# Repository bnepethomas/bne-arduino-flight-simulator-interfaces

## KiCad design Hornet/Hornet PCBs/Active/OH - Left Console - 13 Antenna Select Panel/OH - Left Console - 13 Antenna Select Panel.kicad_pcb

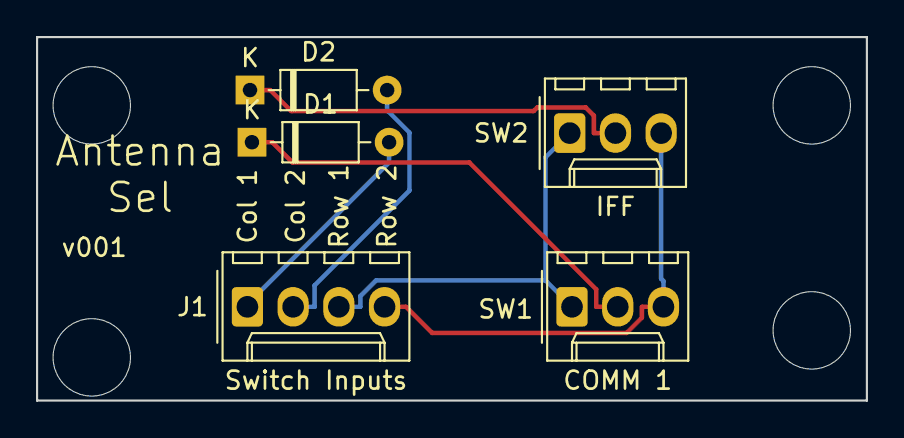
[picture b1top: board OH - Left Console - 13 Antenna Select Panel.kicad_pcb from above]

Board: 2 copper layers, 46.1 x 20.2 mm, 9 parts (0 on the bottom side), 6 nets.

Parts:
D1, D2: D; D_Signal_P7.62mm_Horizontal
H1, H2, H3, H4: MountingHole; MountingHole_4.3mm_M4
J1: Switch Inputs; Molex_1x04_P2.54mm_Vertical
SW1: COMM 1; Molex_1x03_P2.54mm_Vertical
SW2: IFF; Molex_1x03_P2.54mm_Vertical

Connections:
/Col1: D1.2, J1.1
/Col2: D2.2, J1.2
/Row1: J1.3, SW1.1, SW2.1
/Row2: J1.4, SW1.3, SW2.3
unnamed: D1.1, SW1.2
unnamed: D2.1, SW2.2

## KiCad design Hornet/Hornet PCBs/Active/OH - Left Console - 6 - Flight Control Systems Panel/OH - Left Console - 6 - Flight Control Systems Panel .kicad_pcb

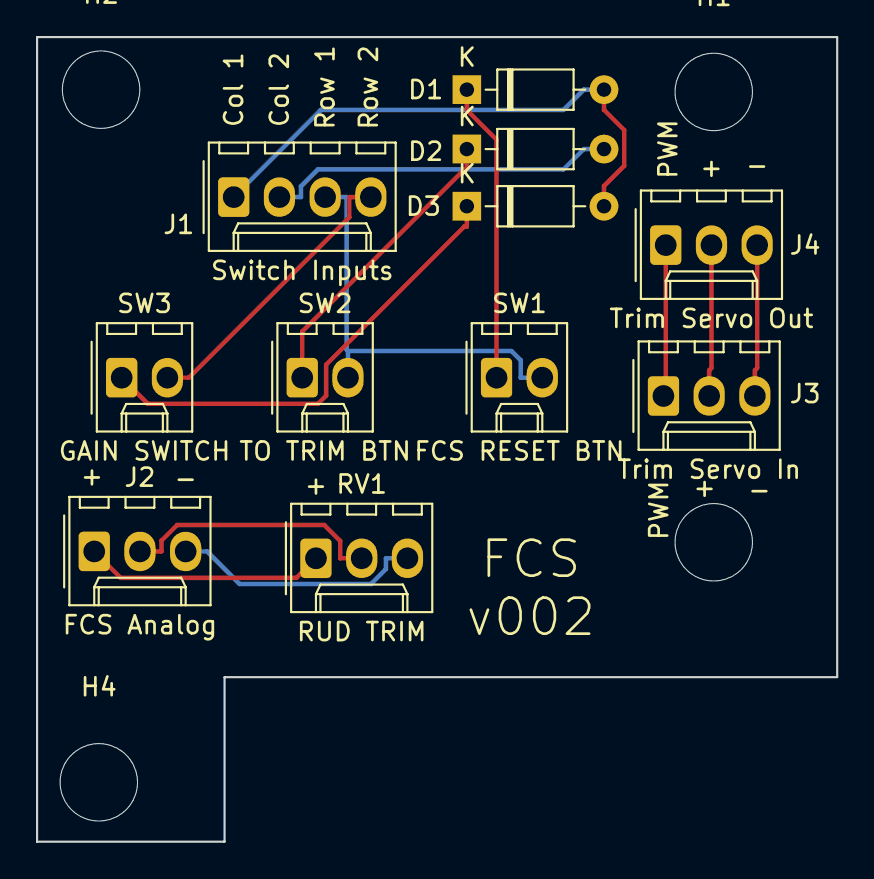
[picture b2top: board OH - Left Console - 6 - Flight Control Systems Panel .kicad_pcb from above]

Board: 2 copper layers, 44.5 x 44.7 mm, 15 parts (0 on the bottom side), 13 nets.

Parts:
D1, D2, D3: D; D_DO-35_SOD27_P7.62mm_Horizontal
H1, H2, H3, H4: MountingHole; MountingHole_4.3mm_M4
J1: Switch Inputs; Molex_1x04_P2.54mm_Vertical
J2: FCS Analog; Molex_1x03_P2.54mm_Vertical
J3: Trim Servo In; Molex_1x03_P2.54mm_Vertical
J4: Trim Servo Out; Molex_1x03_P2.54mm_Vertical
RV1: RUD TRIM; Molex_1x03_P2.54mm_Vertical
SW1: FCS RESET BTN; Molex_1x02_P2.54mm_Vertical
SW2: TO TRIM BTN; Molex_1x02_P2.54mm_Vertical
SW3: GAIN SWITCH; Molex_1x02_P2.54mm_Vertical

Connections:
/Analog+5V: J2.1, RV1.1
/Analog_Gnd: J2.3, RV1.3
/Col1: D1.2, D3.2, J1.1
/Col2: D2.2, J1.2
/Row1: J1.3, SW1.2, SW2.2
/Row2: J1.4, SW3.2
/Rud_Trim: J2.2, RV1.2
/SERVO_5V: J3.2, J4.2
/SERVO_GND: J3.3, J4.3
/TRIM_SERVO_SIG: J3.1, J4.1
unnamed: D1.1, SW1.1
unnamed: D2.1, SW2.1
unnamed: D3.1, SW3.1

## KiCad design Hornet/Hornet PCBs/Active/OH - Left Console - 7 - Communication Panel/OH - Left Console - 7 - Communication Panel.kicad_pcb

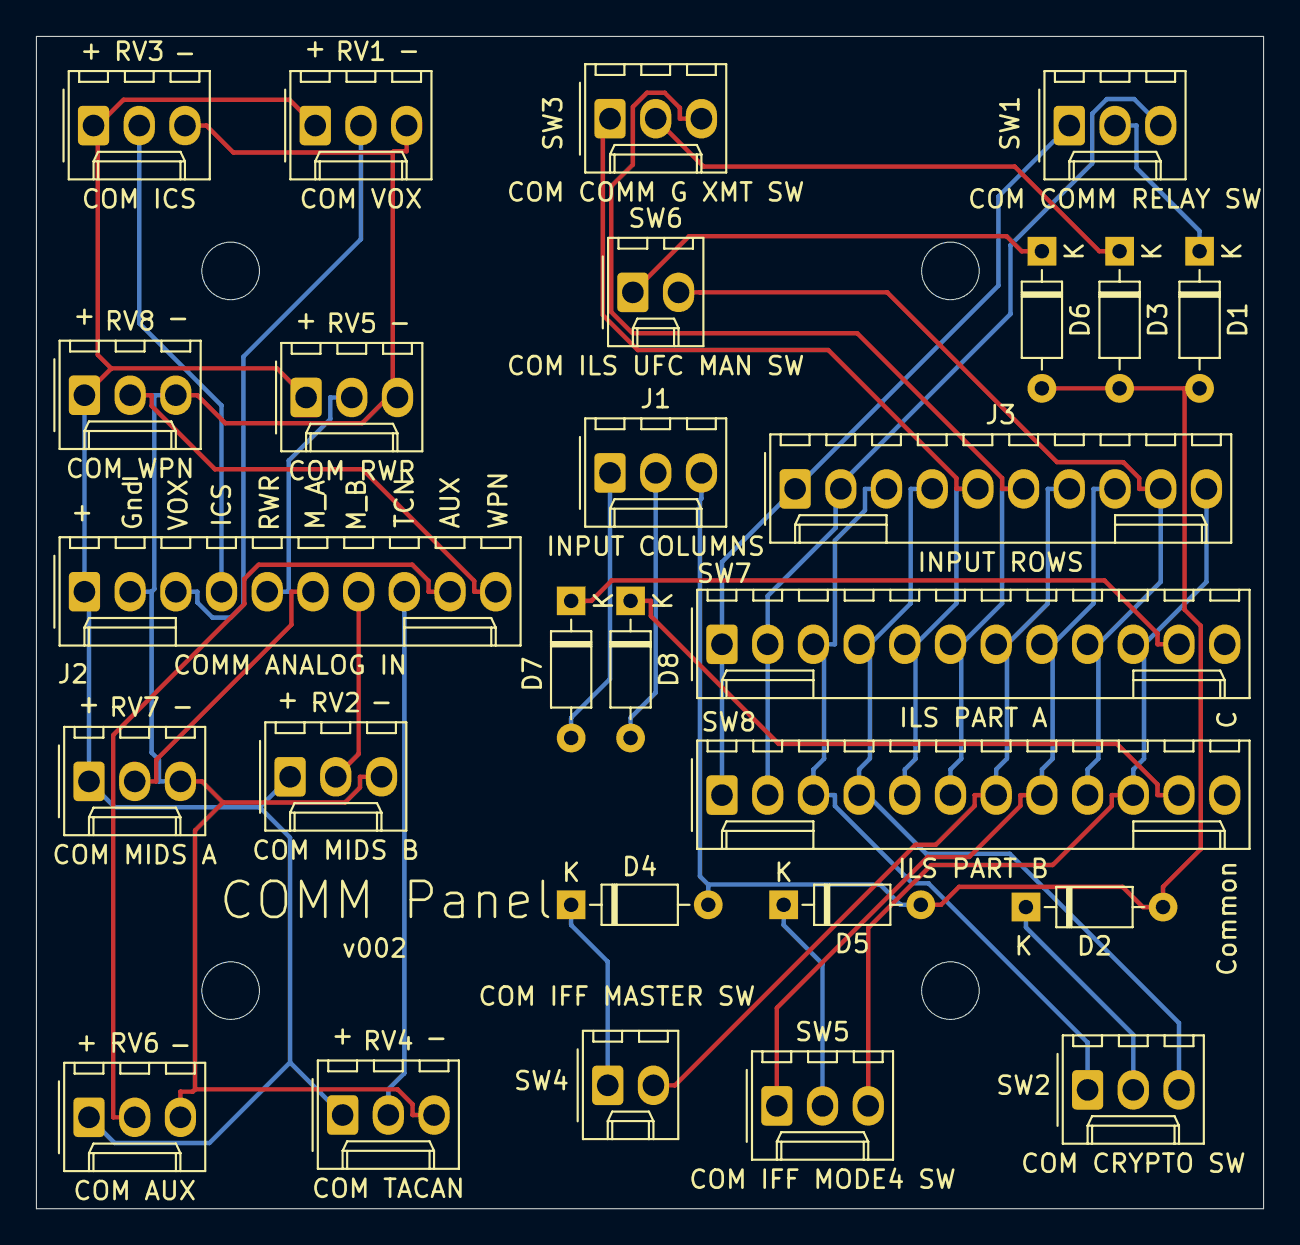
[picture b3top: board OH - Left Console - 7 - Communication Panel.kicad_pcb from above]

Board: 2 copper layers, 68.2 x 65.2 mm, 31 parts (0 on the bottom side), 31 nets.

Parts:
D1, D2, D3, D4, D5, D6, D7, D8: D; D_Signal_P7.62mm_Horizontal
H1, H2, H3, H4: MountingHole; MountingHole_3.2mm_M3
J1: INPUT COLUMNS; Molex_1x03_P2.54mm_Vertical
J2: COMM ANALOG IN; Molex_1x10_P2.54mm_Vertical
J3: INPUT ROWS; Molex_1x10_P2.54mm_Vertical
RV1: COM VOX; Molex_1x03_P2.54mm_Vertical
RV2: COM MIDS B; Molex_1x03_P2.54mm_Vertical
RV3: COM ICS; Molex_1x03_P2.54mm_Vertical
RV4: COM TACAN; Molex_1x03_P2.54mm_Vertical
RV5: COM RWR; Molex_1x03_P2.54mm_Vertical
RV6: COM AUX; Molex_1x03_P2.54mm_Vertical
RV7: COM MIDS A; Molex_1x03_P2.54mm_Vertical
RV8: COM_WPN; Molex_1x03_P2.54mm_Vertical
SW1: COM COMM RELAY SW; Molex_1x03_P2.54mm_Vertical
SW2: COM CRYPTO SW; Molex_1x03_P2.54mm_Vertical
SW3: COM COMM G XMT SW; Molex_1x03_P2.54mm_Vertical
SW4: COM IFF MASTER SW; Molex_1x02_P2.54mm_Vertical
SW5: COM IFF MODE4 SW; Molex_1x03_P2.54mm_Vertical
SW6: COM ILS UFC MAN SW; Molex_1x02_P2.54mm_Vertical
SW7: ILS PART A; Molex_KK-254_AE-6410-12A_1x12_P2.54mm_Vertical
SW8: ILS PART B; Molex_KK-254_AE-6410-12A_1x12_P2.54mm_Vertical

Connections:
/ANALOG_5V: J2.1, RV1.1, RV2.1, RV3.1, RV4.1, RV5.1, RV6.1, RV7.1, RV8.1
/ANALOG_GND: J2.2, RV1.3, RV2.3, RV3.3, RV4.3, RV5.3, RV6.3, RV7.3, RV8.3
/COL1: D7.2, J1.1
/COL2: D8.2, J1.2
/COL3: D1.2, D2.2, D3.2, D4.2, D5.2, D6.2, J1.3
/COM_AUX: J2.9, RV6.2
/COM_ICS: J2.4, RV3.2
/COM_MIDS_A: J2.6, RV7.2
/COM_MIDS_B: J2.7, RV2.2
/COM_RWR: J2.5, RV5.2
/COM_TACAN: J2.8, RV4.2
/COM_VOX: J2.3, RV1.2
/COM_WPN: J2.10, RV8.2
/ROW1: J3.1, SW1.1, SW7.1, SW8.1
/ROW2: J3.2, SW1.3, SW7.2, SW8.2
/ROW3: J3.3, SW2.1, SW7.3, SW8.3
/ROW4: J3.4, SW2.3, SW7.4, SW8.4
/ROW5: J3.5, SW3.1, SW7.5, SW8.5
/ROW6: J3.6, SW3.3, SW7.6, SW8.6
/ROW7: J3.7, SW4.2, SW7.7, SW8.7
/ROW8: J3.8, SW5.1, SW7.8, SW8.8
/ROW9: J3.9, SW6.2, SW7.9, SW8.9
/ROW10: J3.10, SW5.3, SW7.10, SW8.10
unnamed: D1.1, SW1.2
unnamed: D2.1, SW2.2
unnamed: D3.1, SW3.2
unnamed: D4.1, SW4.1
unnamed: D5.1, SW5.2
unnamed: D6.1, SW6.1
unnamed: D7.1, SW7.11
unnamed: D8.1, SW8.11

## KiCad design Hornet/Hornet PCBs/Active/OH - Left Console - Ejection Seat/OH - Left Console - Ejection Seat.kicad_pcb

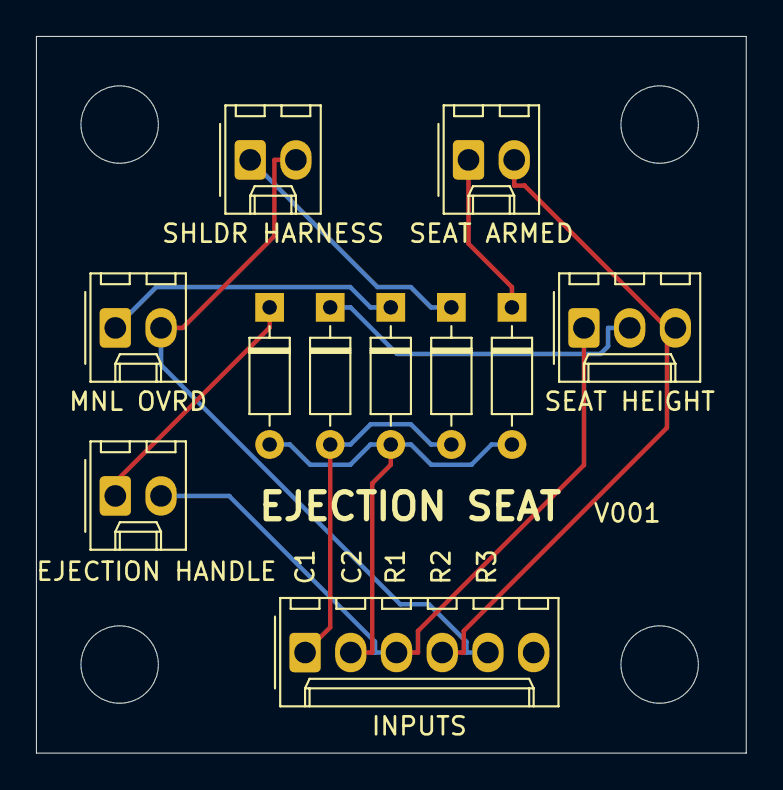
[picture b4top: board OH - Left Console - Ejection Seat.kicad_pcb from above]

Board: 2 copper layers, 39.4 x 39.8 mm, 15 parts (0 on the bottom side), 10 nets.

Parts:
D1, D2, D3, D4, D5: D; D_Signal_P7.62mm_Horizontal
H1, H2, H3, H4: MountingHole; MountingHole_4.3mm_M4
J1: INPUTS; Molex_1x06_P2.54mm_Vertical
SW1: EJECTION HANDLE; Molex_1x02_P2.54mm_Vertical
SW2: SEAT ARMED; Molex_1x02_P2.54mm_Vertical
SW3: MNL OVRD; Molex_1x02_P2.54mm_Vertical
SW4: SEAT HEIGHT; Molex_1x03_P2.54mm_Vertical
SW5: SHLDR HARNESS; Molex_1x02_P2.54mm_Vertical

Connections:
/Col1: D4.2, D5.2, J1.1
/Row1: J1.3, SW1.2, SW4.1
/Row2: J1.4, SW2.2, SW4.3
/Row3: J1.5, SW3.2, SW5.2
unnamed: D1.1, SW1.1
unnamed: D1.2, D2.2, D3.2, J1.2
unnamed: D2.1, SW2.1
unnamed: D3.1, SW3.1
unnamed: D4.1, SW4.2
unnamed: D5.1, SW5.1

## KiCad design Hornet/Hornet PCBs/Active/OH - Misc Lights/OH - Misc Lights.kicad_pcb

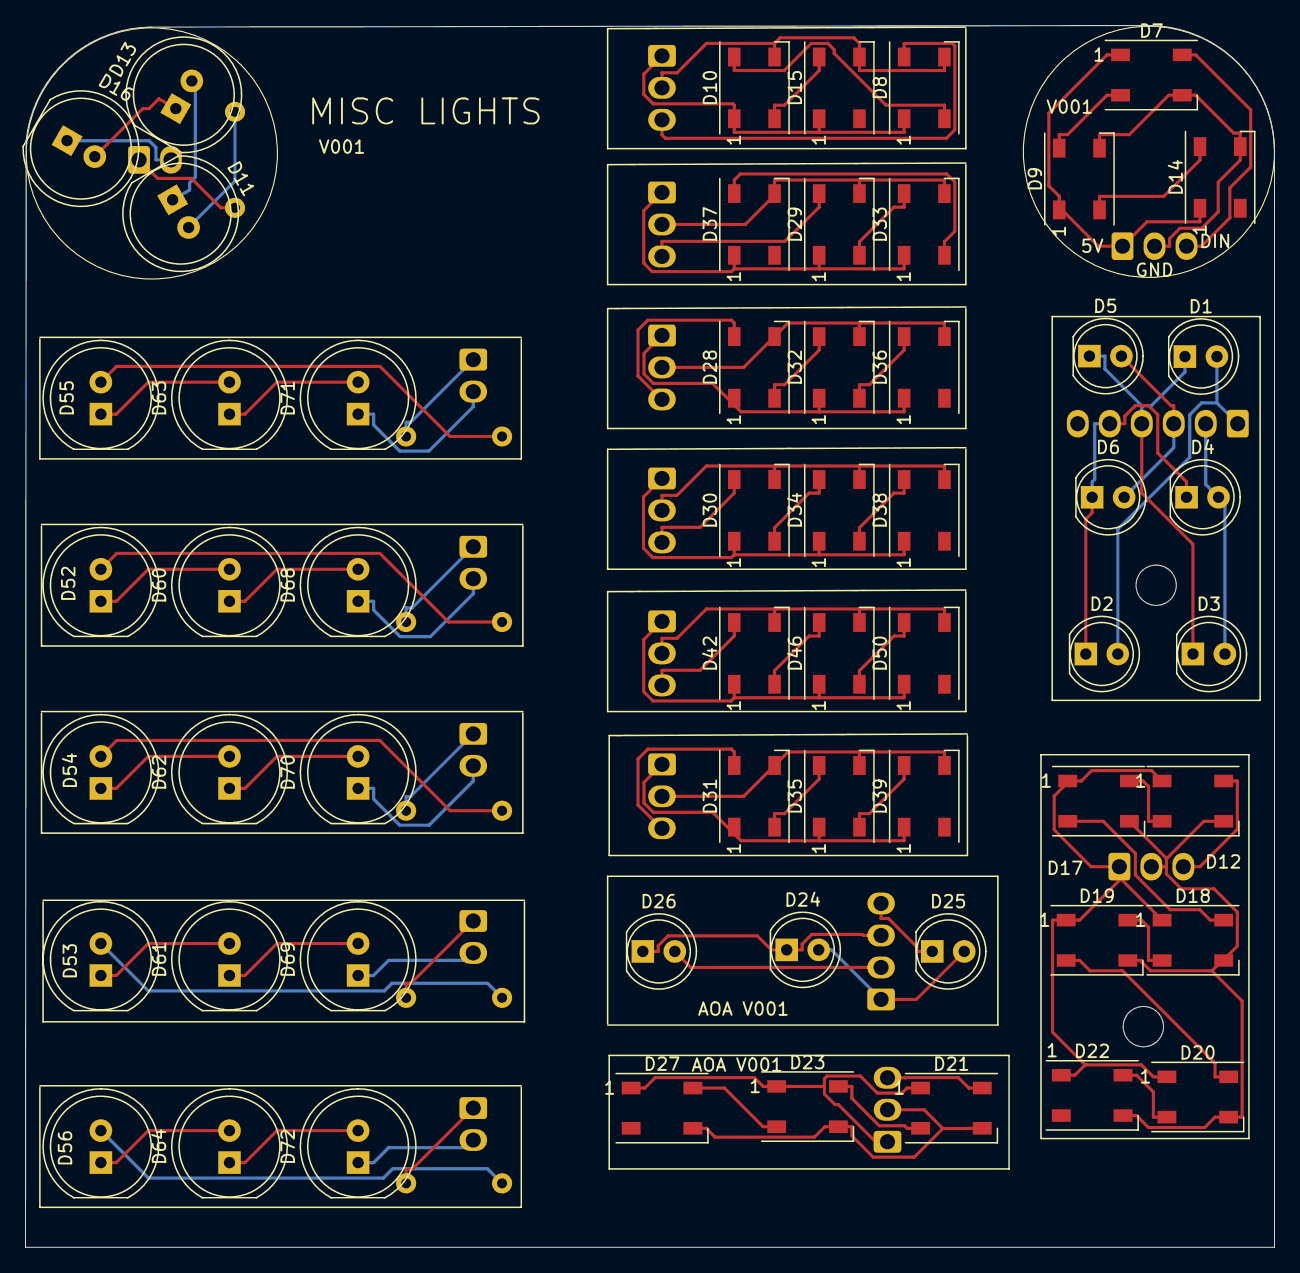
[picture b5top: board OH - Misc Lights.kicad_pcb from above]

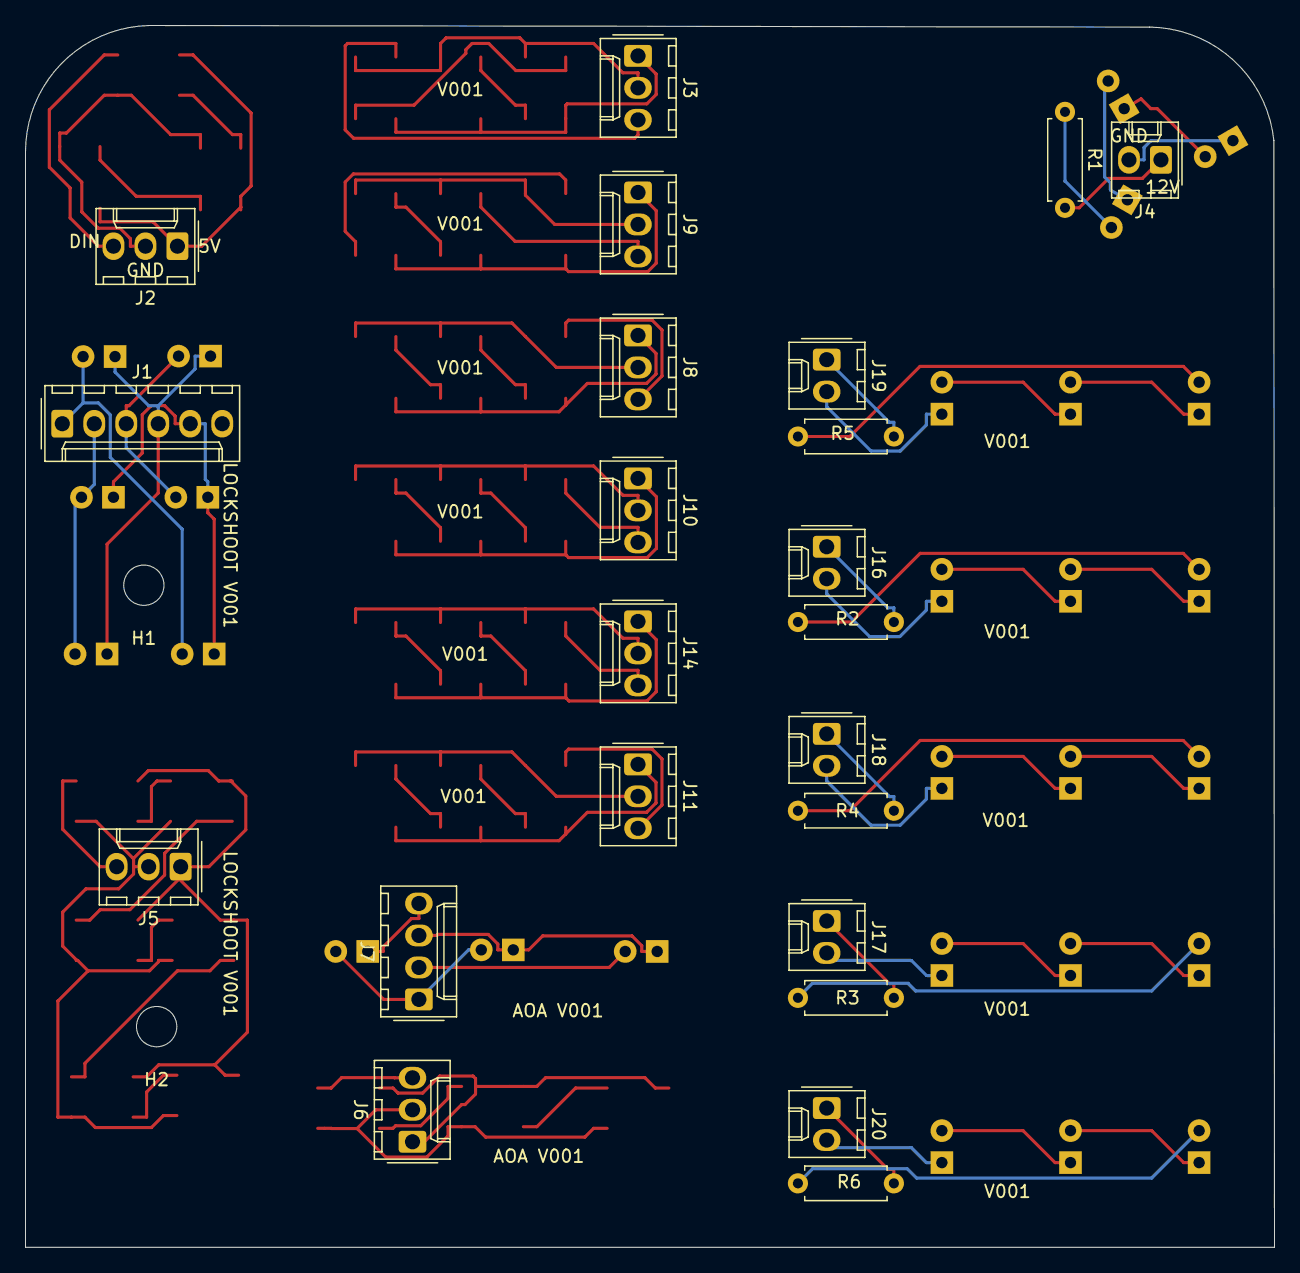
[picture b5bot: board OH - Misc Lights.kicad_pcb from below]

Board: 2 copper layers, 99.2 x 97.0 mm, 82 parts (25 on the bottom side), 87 nets.

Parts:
D1, D2, D3, D4, D5, D6, D24, D25, D26: LED; LED_D5.0mm
D7, D8, D9, D10, D12, D14, D15, D17, D18, D19, D20, D21, D22, D23, D27, D28, D29, D30, D31, D32, D33, D34, D35, D36, D37, D38, D39, D42, D46, D50: WS2812B; LED_WS2812B_PLCC4_5.0x5.0mm_P3.2mm
D11, D13, D16, D52, D53, D54, D55, D56, D60, D61, D62, D63, D64, D68, D69, D70, D71, D72: LED; LED_D8.0mm
H1, H2: MountingHole; MountingHole_3.2mm_M3
J1: Conn_01x06_Female; Molex_1x06_P2.54mm_Vertical
J2, J3, J5, J6, J8, J9, J10, J11, J14: Conn_01x03_Female; Molex_1x03_P2.54mm_Vertical
J4, J16, J17, J18, J19, J20: Conn_01x02_Female; Molex_1x02_P2.54mm_Vertical
J7: Conn_01x04_Female; Molex_1x04_P2.54mm_Vertical
R1, R2, R3, R4, R5, R6: R_US; R_Axial_DIN0207_L6.3mm_D2.5mm_P7.62mm_Horizontal

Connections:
/AOA_2812_+5V: D21.1, D23.1, D27.1, J6.1
/AOA_2812_GND: D21.3, D23.3, D27.3, J6.2
/AOA_2812_IN: D21.4, J6.3
/AOA_COL1: D24.2, D25.2, J7.1
/AOA_COL2: D26.2, J7.2
/AOA_ROW1: D24.1, D26.1, J7.3
/AOA_ROW2: D25.1, J7.4
/CHART_5V: J4.1, R1.2
/CHART_GND: D16.1, J4.2
/Col1: D1.2, D2.2, J1.1
/Col2: D3.2, D4.2, J1.2
/Col3: D5.2, D6.2, J1.3
/FLOOD_2812_+5V: D7.1, D9.1, D14.1, J2.1
/FLOOD_2812_GND: D7.3, D9.3, D14.3, J2.2
/FLOOD_2812_IN: D7.4, J2.3
/LOCKSHOOT_2812_+5V: D12.1, D17.1, D18.1, D19.1, D20.1, D22.1, J5.1
/LOCKSHOOT_2812_GND: D12.3, D17.3, D18.3, D19.3, D20.3, D22.3, J5.2
/LOCKSHOOT_IN: D12.4, J5.3
/Row1: D1.1, D3.1, D5.1, J1.4
/Row2: D2.1, D4.1, D6.1, J1.5
unnamed: D7.2, D9.4
unnamed: D8.4, J3.3
unnamed: D8.1, D10.1, D15.1, J3.1
unnamed: D10.2, D15.4
unnamed: D8.3, D10.3, D15.3, J3.2
unnamed: D8.2, D10.4
unnamed: D11.1, D13.2
unnamed: D11.2, R1.1
unnamed: D12.2, D17.4
unnamed: D13.1, D16.2
unnamed: D9.2, D14.4
unnamed: D17.2, D18.4
unnamed: D18.2, D19.4
unnamed: D19.2, D20.4
unnamed: D20.2, D22.4
unnamed: D21.2, D23.4
unnamed: D23.2, D27.4
unnamed: D28.1, D32.1, D36.1, J8.1
unnamed: D28.2, D32.4
unnamed: D28.3, D32.3, D36.3, J8.2
unnamed: D28.4, J8.3
unnamed: D29.1, D33.1, D37.1, J9.1
unnamed: D29.2, D33.4
unnamed: D29.3, D33.3, D37.3, J9.2
unnamed: D29.4, J9.3
unnamed: D30.1, D34.1, D38.1, J10.1
unnamed: D30.2, D34.4
unnamed: D30.3, D34.3, D38.3, J10.2
unnamed: D30.4, J10.3
unnamed: D31.1, D35.1, D39.1, J11.1
unnamed: D31.2, D35.4
unnamed: D31.3, D35.3, D39.3, J11.2
unnamed: D31.4, J11.3
unnamed: D32.2, D36.4
unnamed: D33.2, D37.4
unnamed: D34.2, D38.4
unnamed: D35.2, D39.4
unnamed: D42.1, D46.1, D50.1, J14.1
unnamed: D42.2, D46.4
unnamed: D42.3, D46.3, D50.3, J14.2
unnamed: D42.4, J14.3
unnamed: D46.2, D50.4
unnamed: D52.1, D60.2
unnamed: D52.2, R2.1
unnamed: D53.1, D61.2
unnamed: D53.2, R3.1
unnamed: D54.1, D62.2
unnamed: D54.2, R4.1
unnamed: D55.1, D63.2
unnamed: D55.2, R5.1
unnamed: D56.1, D64.2
unnamed: D56.2, R6.1
unnamed: D60.1, D68.2
unnamed: D61.1, D69.2
unnamed: D62.1, D70.2
unnamed: D63.1, D71.2
unnamed: D64.1, D72.2
unnamed: D68.1, J16.2
unnamed: D69.1, J17.2
unnamed: D70.1, J18.2
unnamed: D71.1, J19.2
unnamed: D72.1, J20.2
unnamed: J16.1, R2.2
unnamed: J17.1, R3.2
unnamed: J18.1, R4.2
unnamed: J19.1, R5.2
unnamed: J20.1, R6.2

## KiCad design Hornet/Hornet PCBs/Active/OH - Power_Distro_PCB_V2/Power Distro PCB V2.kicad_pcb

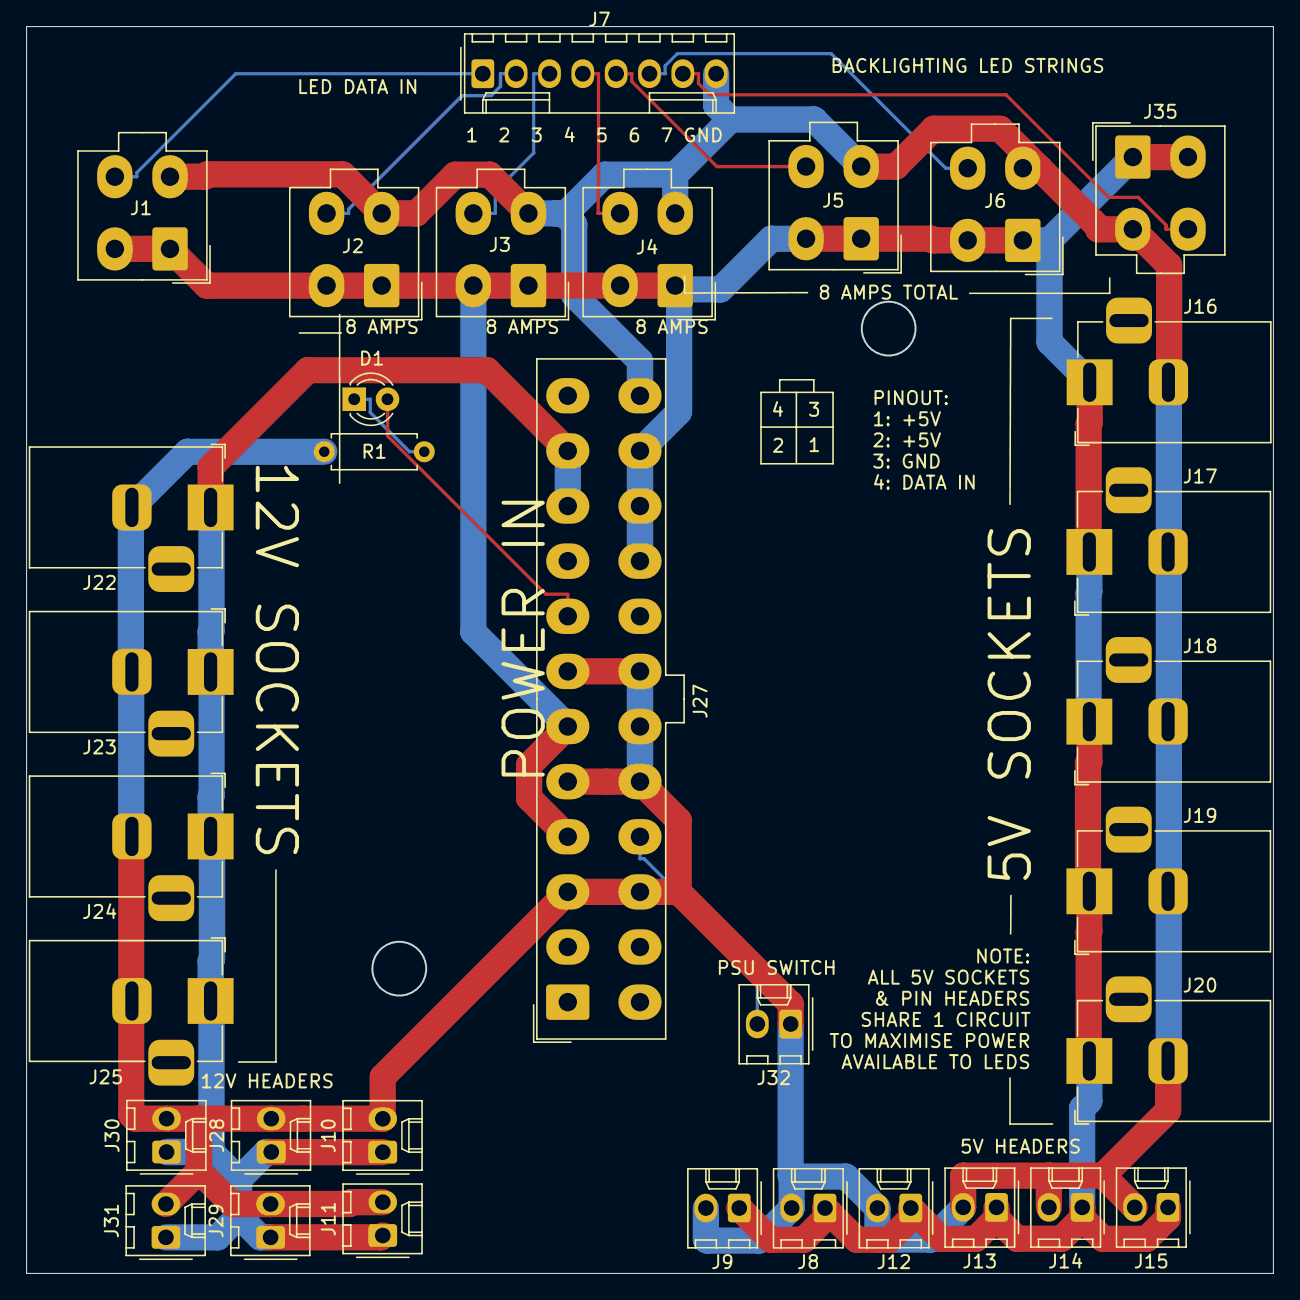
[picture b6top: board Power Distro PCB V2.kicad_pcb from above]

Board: 2 copper layers, 95.0 x 95.0 mm, 33 parts (0 on the bottom side), 13 nets.

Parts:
D1: LED; LED_D3.0mm
J1, J2, J3, J4, J5, J6, J35: Conn_01x04_Female; Molex_Mini-Fit_Jr_5566-04A_2x02_P4.20mm_Vertical
J7: Conn_01x08_Female; Molex_1x08_P2.54mm_Vertical
J8, J9, J10, J11, J12, J13, J14, J15, J28, J29, J30, J31, J32: Conn_01x02_Female; Molex_KK-254_AE-6410-02A_1x02_P2.54mm_Vertical
J16, J17, J18, J19, J20, J22, J23, J24, J25: Conn_01x02_Female; BarrelJack_Horizontal
J27: Conn_01x24_Female; Molex_Mini-Fit_Jr_5566-24A_2x12_P4.20mm_Vertical
R1: R; R_Axial_DIN0207_L6.3mm_D2.5mm_P7.62mm_Horizontal

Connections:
/12VSOCKETS+: J10.1, J11.1, J22.1, J23.1, J24.1, J25.1, J27.10, J27.11, J28.1, J29.1, J30.1, J31.1
/LED5V1: J1.1, J1.2, J2.1, J2.2, J3.1, J3.2, J4.1, J4.2, J5.1, J5.2, J6.1, J6.2, J8.1, J9.1, J12.1, J13.1, J14.1, J15.1, J16.1, J17.1, J18.1, J19.1, J20.1, J27.4, J27.6, J27.21, J27.22, J27.23, J35.1, J35.2
/LEDDATA1: J1.4, J7.1
/LEDDATA2: J2.4, J7.2
/LEDDATA3: J3.4, J7.3
/LEDDATA4: J4.4, J7.4
/LEDDATA5: J5.4, J7.5
/LEDDATA6: J6.4, J7.6
/LEDDATA7: J7.7, J35.4
/LEDGND: J1.3, J2.3, J3.3, J4.3, J5.3, J6.3, J7.8, J8.2, J9.2, J10.2, J11.2, J12.2, J13.2, J14.2, J15.2, J16.2, J17.2, J18.2, J19.2, J20.2, J22.2, J23.2, J24.2, J25.2, J27.3, J27.5, J27.7, J27.15, J27.17, J27.18, J27.19, J27.24, J28.2, J29.2, J30.2, J31.2, J32.1, J35.3, R1.1
/PSUSW: J27.16, J32.2
/PWRGOOD: D1.2, J27.8
unnamed: D1.1, R1.2

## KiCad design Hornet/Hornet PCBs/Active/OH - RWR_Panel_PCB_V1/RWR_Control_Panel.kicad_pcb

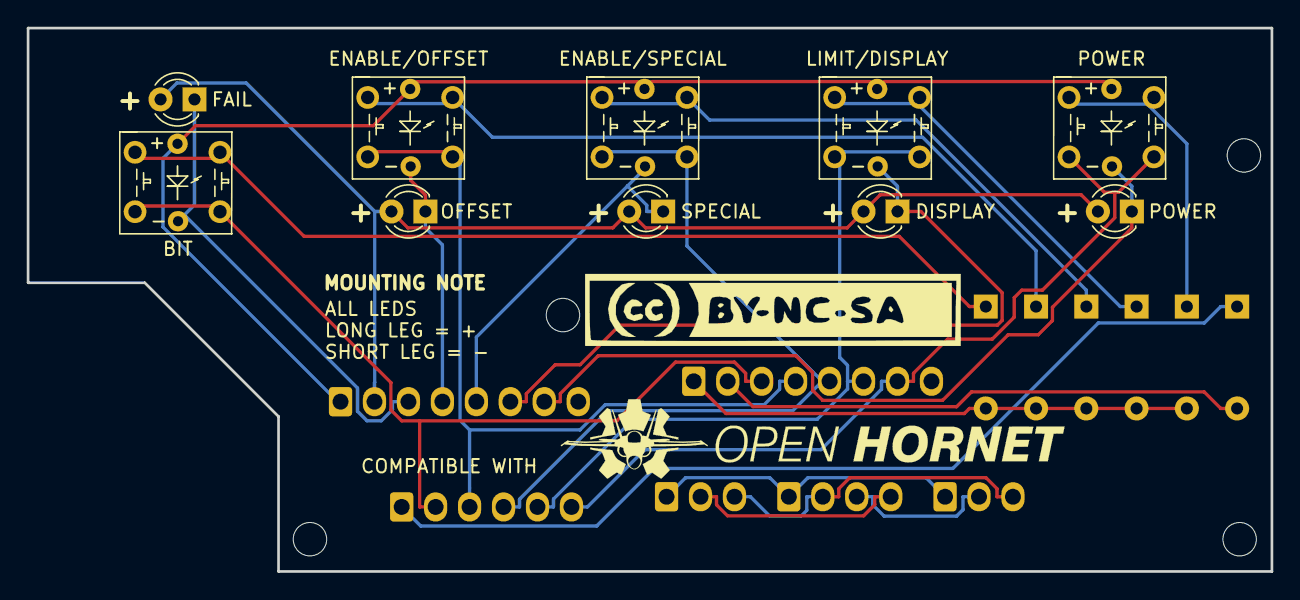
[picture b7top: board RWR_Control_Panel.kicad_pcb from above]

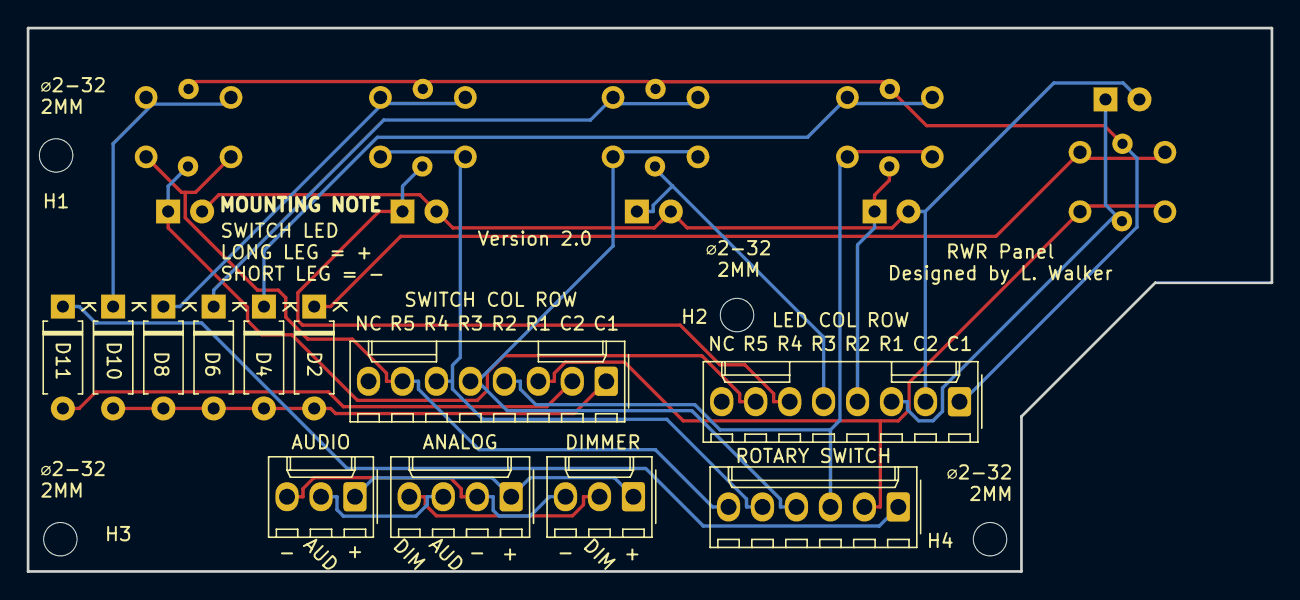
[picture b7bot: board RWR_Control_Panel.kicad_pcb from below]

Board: 2 copper layers, 93.0 x 40.6 mm, 26 parts (12 on the bottom side), 24 nets.

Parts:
BIT: PT_Tactile_Switch_Led; PT_Small_Tactile_Switch_With_LED
D1: FAIL; LED_D3.0mm
D2, D4, D6, D8, D10, D11: D; D_A-405_P7.62mm_Horizontal
D3: OFFSET; LED_D3.0mm
D5: SPECIAL; LED_D3.0mm
D7: DISPLAY; LED_D3.0mm
D9: POWER; LED_D3.0mm
ENABLE/OFFSET: PT_Tactile_Switch_Led; PT_Small_Tactile_Switch_With_LED
ENABLE/SPECIAL: PT_Tactile_Switch_Led; PT_Small_Tactile_Switch_With_LED
J1: LED COL ROW; Molex_KK-254_AE-6410-08A_1x08_P2.54mm_Vertical
J2: DIMMER; Molex_KK-254_AE-6410-03A_1x03_P2.54mm_Vertical
J3: AUDIO; Molex_KK-254_AE-6410-03A_1x03_P2.54mm_Vertical
J4: ROTARY SWITCH; Molex_KK-254_AE-6410-06A_1x06_P2.54mm_Vertical
J5: ANALOG; Molex_KK-254_AE-6410-04A_1x04_P2.54mm_Vertical
J6: SWITCH COL ROW; Molex_KK-254_AE-6410-08A_1x08_P2.54mm_Vertical
LIMIT/DISPLAY: PT_Tactile_Switch_Led; PT_Small_Tactile_Switch_With_LED
P3, P4, P5, P6: CONN_01X01; MountingHole_2.5mm
POWER: PT_Tactile_Switch_Led; PT_Small_Tactile_Switch_With_LED

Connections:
/Analog5V: J2.1, J3.1, J5.1
/AnalogAudio: J2.2, J5.3
/AnalogDimmer: J3.2, J5.4
/AnalogGND: J2.3, J3.3, J5.2
/Col1: D2.2, D4.2, D6.2, D8.2, D10.2, J6.1
/Col2: D11.2, J6.2
/Row1: BIT.3, BIT.4, J4.2, J6.3
/Row2: ENABLE/OFFSET.3, ENABLE/OFFSET.4, J4.3, J6.4
/Row3: ENABLE/SPECIAL.3, ENABLE/SPECIAL.4, J4.4, J6.5
/Row4: J4.5, J6.6, LIMIT/DISPLAY.3, LIMIT/DISPLAY.4
/Row5: J4.6, J6.7, POWER.3, POWER.4
/ledcol1: BIT.5, ENABLE/OFFSET.5, ENABLE/SPECIAL.5, J1.1, LIMIT/DISPLAY.5, POWER.5
/ledcol2: D1.2, D3.2, D5.2, D7.2, D9.2, J1.2
/ledrow1: BIT.6, D1.1, J1.3
/ledrow2: D3.1, ENABLE/OFFSET.6, J1.4
/ledrow3: D5.1, ENABLE/SPECIAL.6, J1.5
/ledrow4: D7.1, J1.6, LIMIT/DISPLAY.6
/ledrow5: D9.1, J1.7, POWER.6
unnamed: BIT.1, BIT.2, D2.1
unnamed: D4.1, ENABLE/OFFSET.1, ENABLE/OFFSET.2
unnamed: D6.1, ENABLE/SPECIAL.1, ENABLE/SPECIAL.2
unnamed: D8.1, LIMIT/DISPLAY.1, LIMIT/DISPLAY.2
unnamed: D10.1, POWER.1, POWER.2
unnamed: D11.1, J4.1

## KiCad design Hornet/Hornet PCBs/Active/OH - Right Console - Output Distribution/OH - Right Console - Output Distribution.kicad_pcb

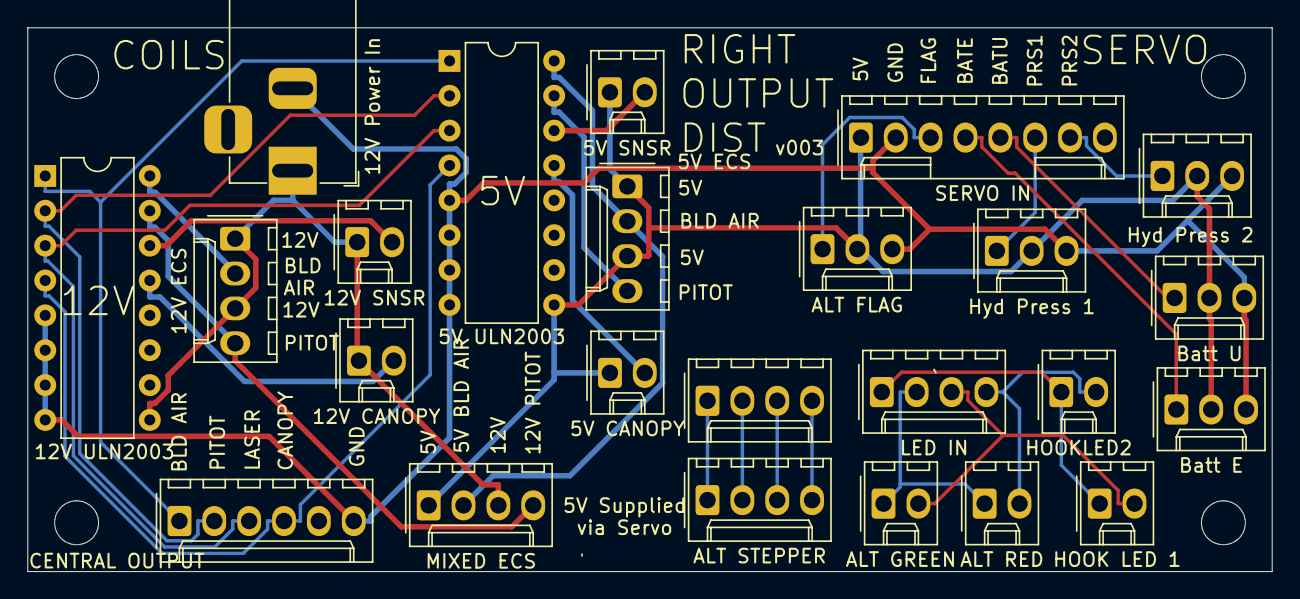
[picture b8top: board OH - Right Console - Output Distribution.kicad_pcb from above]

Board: 2 copper layers, 90.7 x 39.6 mm, 28 parts (0 on the bottom side), 28 nets.

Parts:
H1, H2, H3, H4: MountingHole; MountingHole_3.2mm_M3
J1: CENTRAL OUTPUT; Molex_1x06_P2.54mm_Vertical
J2: SERVO IN; Molex_1x08_P2.54mm_Vertical
J3: 12V Power In; BarrelJack_Horizontal
J4, J7: ALT STEPPER; Molex_1x04_P2.54mm_Vertical
J5: 5V ECS; Molex_1x04_P2.54mm_Vertical
J6: LED IN; Molex_1x04_P2.54mm_Vertical
J8: ALT FLAG; Molex_1x03_P2.54mm_Vertical
J9: HOOK LED 1; Molex_1x02_P2.54mm_Vertical
J10: ALT GREEN; Molex_1x02_P2.54mm_Vertical
J11: HOOKLED2; Molex_1x02_P2.54mm_Vertical
J12: ALT RED; Molex_1x02_P2.54mm_Vertical
J13: 12V ECS; Molex_1x04_P2.54mm_Vertical
J14: 12V SNSR; Molex_1x02_P2.54mm_Vertical
J15: 12V CANOPY; Molex_1x02_P2.54mm_Vertical
J16: Batt U; Molex_1x03_P2.54mm_Vertical
J17: Batt E; Molex_1x03_P2.54mm_Vertical
J18: Hyd Press 1; Molex_1x03_P2.54mm_Vertical
J19: Hyd Press 2; Molex_1x03_P2.54mm_Vertical
J20: 5V SNSR; Molex_1x02_P2.54mm_Vertical
J21: 5V CANOPY; Molex_1x02_P2.54mm_Vertical
J22: MIXED ECS; Molex_1x04_P2.54mm_Vertical
U1: 12V ULN2003; DIP-16_W7.62mm
U2: 5V ULN2003; DIP-16_W7.62mm

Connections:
/5V_Out_Bleed_Air_Sol: J5.2, J22.2, U2.16
/5V_Out_Canopy_Mag: J21.2, U2.13
/5V_Out_Laser_Arm_Mag: J20.2, U2.14
/5V_Out_Pitot_Heat_Mag: J5.4, U2.15
/12V_Out_Bleed_Air_Sol: J13.2, U1.16
/12V_Out_Canopy_Mag: J15.2, U1.13
/12V_Out_Laser_Arm_Mag: J14.2, U1.14
/12V_Out_Pitot_Heat_Mag: J13.4, J22.4, U1.15
/+12V: J3.1, J13.1, J13.3, J14.1, J15.1, J22.3, U1.9
/ALT_FLAG_PWM: J2.3, J8.1
/ALT_STEPPER_1A: J4.1, J7.1
/ALT_STEPPER_1B: J4.2, J7.2
/ALT_STEPPER_2A: J4.3, J7.3
/ALT_STEPPER_2B: J4.4, J7.4
/BATT_E_PWM: J2.4, J17.1
/BATT_U_PWM: J2.5, J16.1
/GND: J1.6, J2.2, J3.2, J8.3, J16.3, J17.3, J18.3, J19.3, U1.5, U1.6, U1.7, U1.8, U2.5, U2.6, U2.7, U2.8
/HYD_PRESS_1_PWM: J2.6, J18.1
/HYD_PRESS_2_PWM: J2.7, J19.1
/In_Bleed_Air_Sol: J1.1, U1.1, U2.1
/In_Canopy_Mag: J1.4, U1.4, U2.4
/In_Laser_Arm_Mag: J1.3, U1.3, U2.3
/In_Pitot_Heat_Mag: J1.2, U1.2, U2.2
/LEDCOL1: J6.3, J9.2, J10.2
/LEDCOL2: J6.4, J11.2, J12.2
/LEDROW1: J6.1, J9.1, J11.1
/LEDROW2: J6.2, J10.1, J12.1
/SERVO_5V: J2.1, J5.1, J5.3, J8.2, J16.2, J17.2, J18.2, J19.2, J20.1, J21.1, J22.1, U2.9

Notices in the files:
Hornet/Hornet PCBs/Active/OH - Power_Distro_PCB_V2/Power Distro PCB V2.kicad_pcb:
© L. Walker 2021
